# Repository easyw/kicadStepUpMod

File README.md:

kicadStepUp-WB
==============

KiCad **StepUp tools** are a FreeCAD Macro and a FreeCAD WorkBench to help in **Mechanical Collaboration** between **KiCad EDA** and **FreeCAD** or a **Mechanical CAD**.

**KiCad StepUp features:** 

- **load kicad board and parts in FreeCAD and export it to STEP** (or IGES) for a full ECAD MCAD collaboration
- **load kicad_mod footprint in FreeCAD to easy and precisely align the mechanical model to kicad footprint**
- **convert the STEP 3D model of parts, board, enclosure to VRML with Materials properties** for the best use in kicad
- **check interference and collisions** for enclosure and footprint design 
- **design a new pcb Edge with FreeCAD Sketcher and PUSH it to an existing kicad_pcb Board** 
- **PULL a pcb Edge from a kicad_pcb Board**, edit it in FC Sketcher and PUSH it back to kicad
- **design a new footprint in FreeCAD to get the power of Sketch in footprints**
- **generate Blender compatible VRML files**
- **translation infrastructure enabled**
- **auto-generate 3D FFC/FPC stiffener geometry from custom PCB user layers**

Please see [KiCad Info forum](https://forum.kicad.info/search?q=stepup) or [FreeCAD forum](https://forum.freecadweb.org/viewtopic.php?f=24&t=14276) to discuss or report issues regarding this Addon.

Installing
----------

Download and install your corresponding version of FreeCAD from [Download page](https://www.freecad.org/downloads) and either install

- automatically using the [FreeCAD Add-on Manager](https://github.com/FreeCAD/FreeCAD-addons) (bundled in to FreeCAD under Tools Menu)
  **(*) There is a known issue in FreeCAD Addons Manager on Linux**

- manually by copying the kicadStepUpMod folder to the Mod sub-directory of the FreeCAD application

- manually by following the standard installation [FreeCAD Installing more workbenches](https://wiki.freecad.org/Installing_more_workbenches)

StepUp Cheat sheet
------------------

[kicad StepUp Cheat sheet](https://github.com/easyw/kicadStepUpMod/raw/master/demo/kicadStepUp-cheat-sheet.pdf)

StepUp Videos
------------------

[ECAD-MCAD-collaboration: Complex Edge Sketch to PCB](https://youtu.be/eMdX3R9ni7g?t=1050)

[ECAD-MCAD-collaboration: Push&Pull Edge to PCB](https://youtu.be/n44iBpu_YjY)

[ECAD MCAD Synchronization: Push & Pull model placement in 3D environment](https://youtu.be/6R6UEUScjgA)

[ECAD-MCAD-collaboration: Footprint in FreeCAD](https://youtu.be/eMdX3R9ni7g?t=839)

[ECAD-MCAD-collaboration: FreeCAD + KiCAD complete walkthrough design](https://www.youtube.com/watch?v=ov3PpaP9uHI)

[ECAD-MCAD-collaboration: Designing a Complex PCB Edge from a 3D model Enclosure](https://www.youtube.com/watch?v=pJCeprBhWLs)

### Requirements

- **FreeCAD** **0.19, 0.20, 0.21, 0.22, 1.0**

- **KiCAD** **5.1**, **6.x**, **7.x**, **8.x**, **9.x**, **10.x**

- **KiCAD *10.99 nigthly* (partially supported)**

### Known issues

- on Linux *FreeCAD Snap and Flatpak* you may need to use 'mount bind' to have access to KiCad 3D models path

- on Linux *FreeCAD Addons* may fail to install (FC >= 1.0.1)

### License

[GNU AFFERO GENERAL PUBLIC LICENSE](https://www.gnu.org/licenses/agpl-3.0.en.html)

### Contributing to kicadStepUp

> :no_entry_sign: **AI-generated contributions are not accepted.** All Pull Requests and issues must be written genuinely by the contributor. :no_entry:We do not accept content (code, comments, commit messages, issue or PR descriptions, documentation, etc.) that is generated by :robot:AI tools. Such contributions will be rejected.

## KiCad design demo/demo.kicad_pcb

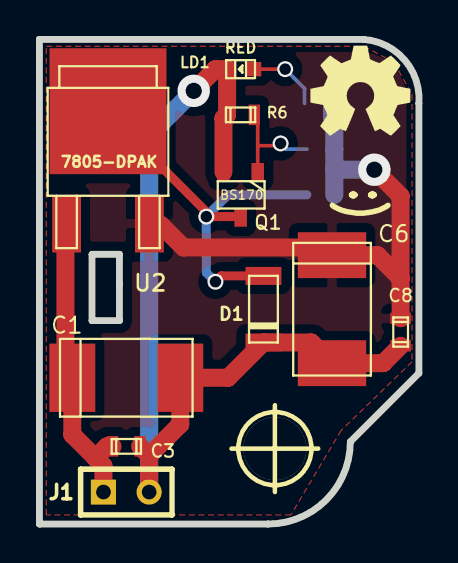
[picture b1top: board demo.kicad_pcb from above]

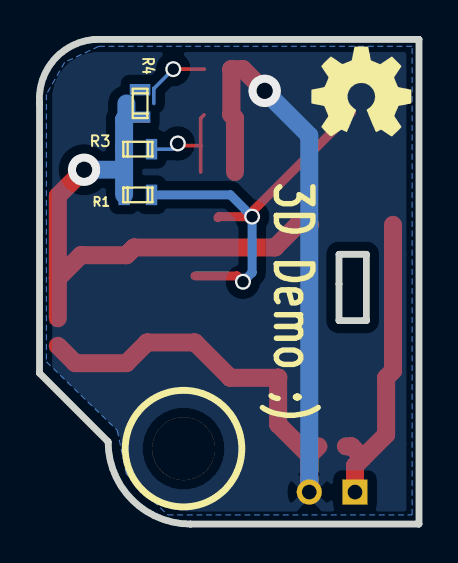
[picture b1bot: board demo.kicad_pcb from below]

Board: 2 copper layers, 21.1 x 26.9 mm, 14 parts (3 on the bottom side), 6 nets.

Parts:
C1, C6: 47u; c_tant_D
C3, C8: 100N; cap_0603
D1: 1N4148; sod80c
J1: Alim; SIL-2
LD1: RED; Led_0603
Q1: BS170; SOT23-GSD
R1, R4: 470; r_0603
R3: 12K; r_0603
R6: 1K; r_0603
U2: 7805-DPAK; d-pak
hole_3mm5: VAL**; hole_3mm5

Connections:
5V: C6.1, C8.1, R1.1, R3.1, R4.1, U2.3
+12V: C1.1, C3.1, J1.1, U2.1
ENP: Q1.1, R3.2, R6.1
GND: C1.2, C3.2, C6.2, C8.2, D1.2, J1.2, LD1.2, Q1.2, R6.2
unnamed: D1.1, Q1.3, R1.2, U2.2
unnamed: LD1.1, R4.2

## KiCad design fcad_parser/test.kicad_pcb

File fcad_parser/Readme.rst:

========================================
Python S-Expression Parser for KiCAD PCB
========================================

Intrudction
___________

The parser ``KicadPCB`` are written using a python S-Expression parser, the
sexp_parser_. To get this submodule, after checkout this repository, do ::

    git submodule init
    git submodule update

The ``KicadPCB`` parser shall be able to handle both ``kicad_pcb`` and
``kicad_mod`` file. The parser does not perform semantic check, though. For
that you'll need to write a large collection of sub-parsers that handle every
possible keyword. It'll be very tedious, but still easy with the help of
``SexpParser``. Check out the `sample code here`_.

.. _sexp_parser:  http://github.com/realthunder/sexp_parser
.. _sample code here: http://github.com/realthunder/sexp_parser/tree/master/test.py

Usage
_____

To get the python object model of a ``kicad_pcb`` or ``kicad_mod`` file ::
    
    from kicad_parser import KicadPCB
    pcb = KicadPCB.load(filename)

Check for error ::

    for e in pcb.getError():
        print('Error: {}'.format(e))

You can modify, add, or delete any expressions inside. You can use ``.`` to
access any non numerical keys such as ::

    pcb.general.zone

For numerical keys, and in fact, all type of keys, you can use ``[]`` ::

    pcb['layers']['0']

Or ::

    pcb.layers['0']

But not ::

    pcb.layers[0]

Because for ``(layers ( 0 F.cu single) ...)`` expression here, the ``0`` is
treated as a string key instead of an integer index. 

For multiple instances with the same key at the same level, you should access
the value by integer index, such as ::

    pcb.module[0]

For un-named values (i.e. any atom behind the key), use their appearance index
for accessing, skipping any named values. For example, to access an expression
like ``(drill oval 1.0 2.0)`` ::

    drill.oval
    drill[0] == 1.0
    drill[1] == 2.0

The 'oval' above would normally be treated as an un-named value, too. However,
``KicadPCB`` treats several special un-named values as named boolean type
value.  Their appearance in the S-Expression source means ``True``, otherwise
means ``False``. These expressions are always accessible through the object
model regardless of their appearance in the source. When doing ``export()``,
those ``False`` values will be ignored. These special values are ::

    gr_text.hide
    pad.drill.oval
    module.locked

This list is obviously not complete. But, it's easy to add your own mappings.
Check out the source code `here <kicad_pcb.py>`_

``KicadPCB`` also treats specal keyword as un-named boolean type, they are ::

    'yes', 'Yes', 'true', 'True', 'no', 'No', 'false', 'False'

To list the sub keys of a composite expression ::

    for subkey in pcb:
        print(subkey)

It will also list integer keys for un-named values if there is any.

To delete an expression ::

    del pcb.layers['0']

To create expressions, you'll need to import the general S-Expression Parser ::

    from kicad_parser import *

For multiple expressions with the same key, they will be stored into an object
of type ``sexp_parser.SexpList`` the parser will automatically create this list
object to hold the multiple instances. To check if it is a list ::

        isinstance(pcb.module,SexpList)

To add a simple expression ``(0 new.layer signal)``, ::

    pcb.layers['0'] = Sexp('0',[ 'new.layer', 'signal' ])

Note that if there is already an expression with the same key, ``=`` will not
overwrite the existing one. Instead, it will use ``SexpList`` to hold multiple
instances

To add a composite expression ::

    pcb.module[0].model = SexpParser(parseSexp(
        """(model new/model3 
            (at (xyz 1 2 3)) 
            (scale (xyz 3 5 6)) 
            (rotate (xyz 7.0 8.0 9.0)))
        """)

If you are not sure whether a key in the object model holds a single expression
or multiple instances, you can use ``SexpList`` to make sure it is a list ::

    if 'module' in pcb:
        for m in SexpList(pcb.module):
            print(m)

``KicadPCB`` will ensure several common keys to be presented even if there is
none, in which case an empty ``SexpList`` will be inserted. And if there is
only one instance, it will still be inside a ``SexpList``.  This is to spare
the pain of the boilerplate code above. The default keys are ::

    net
    net_class
        add_net
    dimension
    gr_text
    gr_line
    gr_circle
    gr_arc
    gr_curve
    segment
    via
    module
        fp_text
        fp_line
        fp_circle
        fp_arc
        pad
        model

To export the modified object model back to kicad_pcb file ::

    pcb.export(filename)

Or to output stream ::

    pcb.export(sys.stdout)

To export any ``Sexp`` ::

    exportSexp(pcb.general,sys.stdout)

See sample code `here <test.py>`_ for more details.

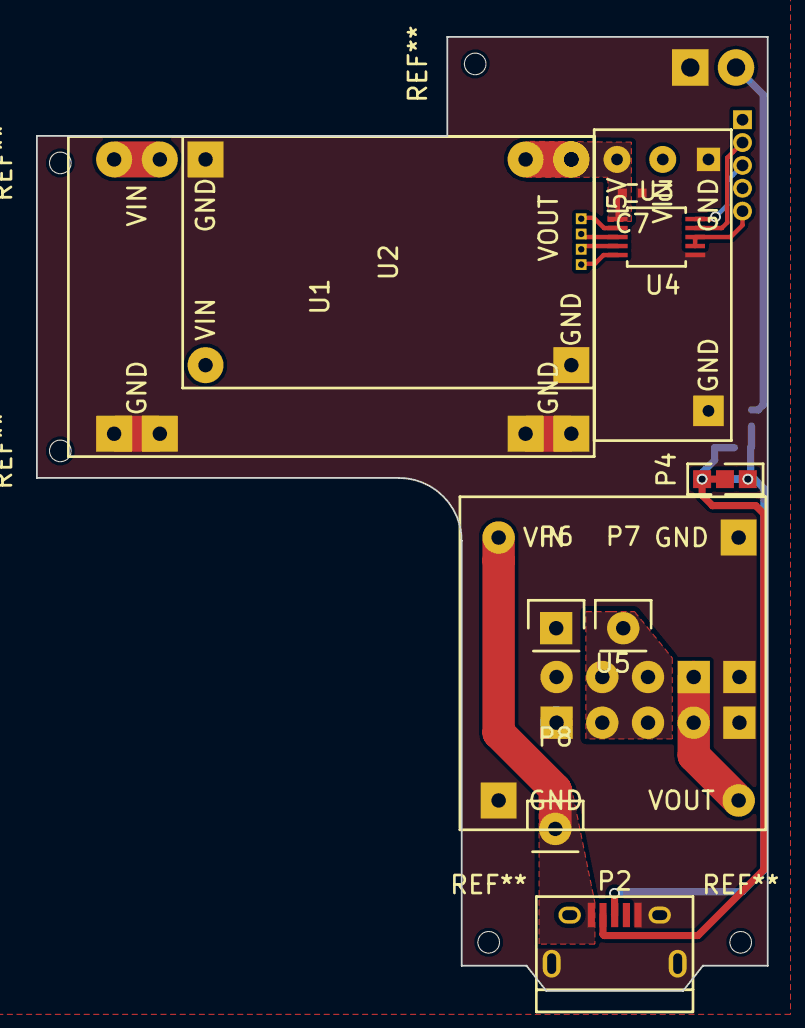
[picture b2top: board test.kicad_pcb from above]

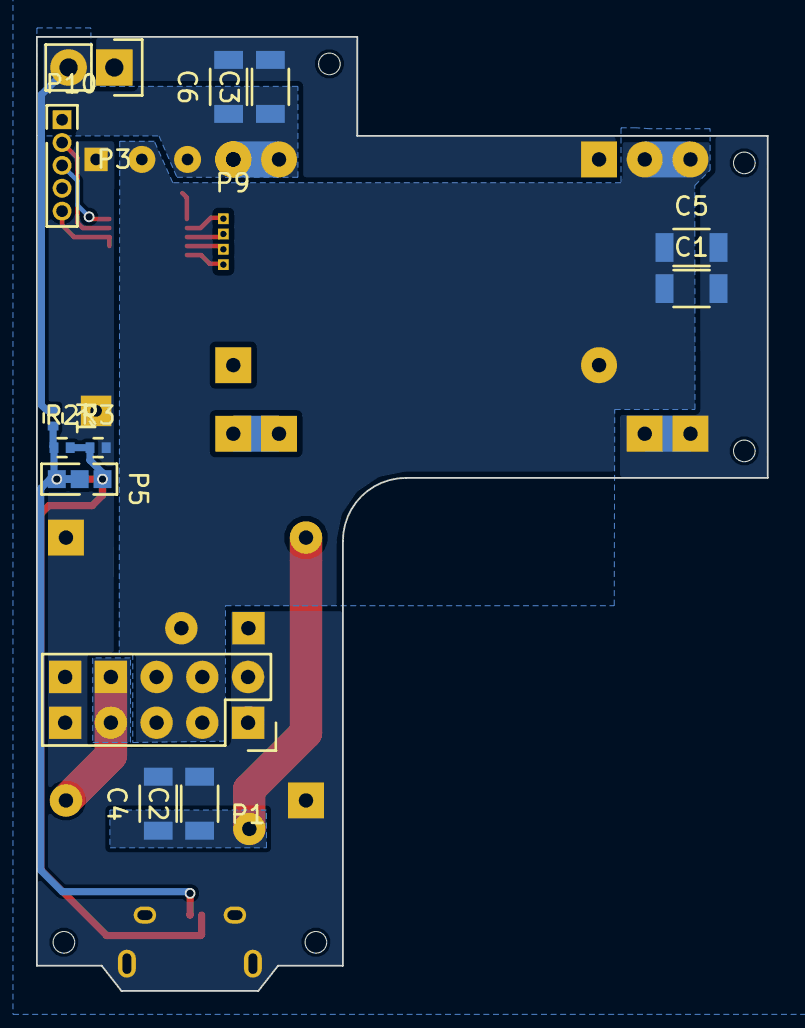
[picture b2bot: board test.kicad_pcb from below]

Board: 2 copper layers, 40.6 x 53.0 mm, 25 parts (14 on the bottom side), 14 nets.

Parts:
C1, C2, C3, C4, C5, C6: 47uF; C_1206
C7: 100nF; C_0402
P1: CONN5; Socket_Strip_Straight_2x05
P2: USB_Micro; USB_Micro-B
P3: CONN_VCC; Socket_Strip_Straight_1x02
P4, P5: CONN_01X03; Pin_Header_Straight_1x03_Pitch1.27mm
P6, P7, P8: CONN_01X01; Pin_Header_Straight_1x01
P9: CONN_01X02; Pin_Header_Straight_1x04_Pitch1.27mm
P10: CONN_01X05; Socket_Strip_Straight_1x05_Pitch1.27mm
R1: 2M; R_0402
R2: 1M; R_0402
R3: 400K; R_0402
U1: TPS61800 module; DCDC_Conv_TPS61088_Boost
U2: G5177 module; DCDC_Conv_G5177-Boost
U3: TMP432; TSSOP-10_3x3mm_Pitch0.5mm
U4: LDO_3V5; LDO_RT9018
U5: TP5000 Charger; DCDC_Charger-TP5000-Bucket

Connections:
/BAT: C1.1, C5.1, P1.3, P1.4, P1.5, P1.6, P7.1, U1.2, U2.2, U4.2
/CHARGE: P1.7, P1.8, U5.3
/CHG_IN: C2.1, C4.1, P2.1, P8.1, U5.2
/D1+: P9.1, U3.2
/D1-: P9.2, U3.3
/D2+: P9.3, U3.4
/D2-: P9.4, U3.5
/SCL1: P10.3, U3.10
/SDA1: P10.2, U3.9
/TMP_INT: P10.5, U3.7, U3.8
/V0.6: P2.2, P4.1, P4.2, P5.1, R2.2, R3.1
/V3.3: P2.3, P4.3, P5.2, P5.3, R1.2, R2.1
GND: C1.2, C2.2, C3.2, C4.2, C5.2, C6.2, C7.1, P1.1, P1.2, P1.9, P1.10, P2.5, P2.6, P3.1, P6.1, R3.2, U1.1, U2.1, U3.6, U4.1, U5.1
VCC: C3.1, C6.1, C7.2, P3.2, R1.1, U1.3, U2.3, U3.1, U4.3

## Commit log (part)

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2020-01-30 allowed import stpz on ksu button
2020-02-10 aligning commit nbr
2020-02-12 taper fp supported in load copper
2020-02-14 final fix for trapezoidal pads
    thx to realthunder
2020-03-13 Multiple 3D model paths
    Add ability to search multiple paths for 3D models.
    Multiple paths can be configured in 'main 3D folder location' and 'secondary 3D folder loc' fields.
    These 2 fields can be comma or carriage return separated lists of paths.
    Currently multiple paths in these fields must be manually entered and not by using the '...' button.
2020-03-14 Import KiCAD prefs environment paths
    New kicadStepUpGui pref 'KiCAD prefs folder' to allow users to select the folder containing file 'kicad_common'.
    File 'kicad_common' is parsed for environment variables with absolute paths.
    The paths are then used to perform substitutions in the 3D model path.
    This modification could make 'main 3D folder location' obsolete since KISYS3DMOD is an entry in the kicad_common file.
    Also since the ALT3DMOD pref now accepts a list of paths (comma or CR separated) then that field can be used to search other external paths for 3D models.
    Note: The preferences panel layout could use some adjustment since they are now a bit compressed together (I don't fully under
2020-04-07 shifting the check for new STEP importer to the end of June
2020-04-12 Allowing simple copy of Body
2020-05-06 improved extra sketches importing
2020-05-07 aligning commit numbers for checking updates
2020-06-25 fixing new github page format
2020-06-30 improved BlackList interface
    allowing height, volume and list parameters in logical 'and'
2020-07-08 implemented fp_rect for fp loading
2020-11-29 Changed regular expression to allow both keywords (footprint and module)
    Fixes #66
2020-11-30 updating kicad parser for 'footprint' and 'module' support (k 5.1 & 5.99)
2020-12-20 fixing fp exporter for 3d path including spaces
2020-12-22 Fix source typos
2020-12-25 minor typo fix
2021-01-29 fixing fill zone area
2021-02-20 updating push&pull 3d models to be compatible with k v5.99
2021-03-05 aligning release nbr
2021-04-08 new RF PolyLined sketcher generator for EM RF sw
2021-04-08 increasing discretization quality for RF conversion
2021-04-21 undo also on reset placement for a shape
2021-08-29 adding NetTie Poly, improved Pads Poly algo, added PTH & NPTH Drills tools for arc in drills, B_Cu layer option for Poly, shape(s) Contour command
2021-08-29 removing extra printing info
2021-08-29 added sample files to Demo Menu folder
2021-08-30 aligning commits
2021-08-31 improving loading fp drills
2021-08-31 cutting tracks outside pcb (castellated holes)
2021-09-03 support for: arc tracks, improved pad resolution and custom pads
2021-09-05 fix Connect Sketch issue
2021-09-06 Internal layers allowed for fp generation (not loading) padNbr for NetTie and Pads_Poly
2021-09-08 adding 3 points center and arc to circle sketch tools
2021-09-09 fixing colors for 2d objects
2021-09-13 second try for fixing Darftmakesketch FC issue
2021-09-15 minor fix in assigning padNbr
2021-09-16 allowing padNum and padNbr tag
2021-09-24 minor fix for pushing keepout zone sketch
2021-09-29 fully integration of fcad_pcb tools from @realthunder
2021-09-29 fix for top tracks and zones z-placement
2021-10-03 Holes for vias are created when importing PCB.
2021-10-19 enabling Transparency in STP color models
2021-10-21 slightly align some color and transparency on materials
2021-10-25 reverting transparency on step export, adding undo on export 3d model
2021-10-27 export 3D STEP models w transparency + minor fix for importing keepout zones
2021-10-28 rem,oving old kicad site references on docs
2021-10-28 aligning version
2021-10-28 keeping transparency for single shape object in 3d exporting materials
2021-10-28 kv6 new arc.mid format compat
2021-10-29 arc rework for pcbnew version >= 20211014
2021-10-30 fixing drill parsing when drill is missing
2021-11-04 fixing offset and oval drills for bottom pads
2021-11-11 adding the solid check in step exporting of a step model
2021-11-15 giving stpz priority to stp in load models
2021-11-17 fixing timestamp push pull
2021-11-22 improving 3d model searching up to 4 paths
2021-11-25 fixinf fp_arc for kv6 format
2021-12-01 minor fix in fp loading for bottom tech layers
2021-12-02 reverting last commit (issues in p.drill parsing)
2021-12-15 utf-8 compat
2021-12-16 fixing utf-8 issue on loading board
2021-12-23 minor fix for turntable and adding xml metafile
2022-01-10 adding Undo on loading pcb/tracks to avoid issues on deleting objects
2022-01-10 Ignore errors when loading primitives
    Loading tracks for my PCB design leads to:
    17:23:32 Running the Python command 'ksuToolsAddTracks' failed:
    Traceback (most recent call last):
    File "/home/user/.FreeCAD/Mod/kicadStepUpMod/kicadStepUpCMD.py", line 3415, in Activated
    tracks.addtracks()
    File "/home/user/.FreeCAD/Mod/kicadStepUpMod/tracks.py", line 346, in addtracks
2022-01-15 fixing zoom fit for tracks
2022-02-19 minor fix on tracks loading (linux)
2022-03-14 fixing pcb thickness = 0 due to new stack feature fixing regression in replacing sketch in board loading
2022-03-17 fixing some push-pull kv6-kv7 format changes
2022-03-19 fixing tracks cutting
2022-03-23 fixing complex sketch pushing
2022-03-23 fixing push complex sketches
2022-04-04 forcing {:.6f}".format for pushing pcb to avoid DRC errors on edge
2022-04-30 fixing parsing pad without drill but with drill offset
2022-05-11 create colored Binder object
2022-05-16 minor improvement in pushing pcb edge
2022-05-31 subshapebinder relinker tool
2022-05-31 updating version
2022-06-13 not showing fp models when 3D model is set to hide
2022-06-27 fixing loading virtual modules for kv >= 6
2022-07-13 improving suggestion for FC import settings (FC0.20+)
2022-07-19 fixing a typo in condition (kSU)
2022-07-22 improving warning for STEP import settings
2022-07-23 Initial commit for translate WB
2022-07-28 fixing add tracks in case of no holes
2022-07-30 avoid error in case of 0-lenght tracks
2022-08-29 fixing Assembly3 Link import option adding Snap Flatpack compatibility hint
2022-08-30 moving LCS to main Board container for a better compatibility with Assembly 4 WB
2022-08-30 fixing report and compare of sketches
2022-09-30 fixing reset placement and virtual objs in kv6
2022-10-03 adding Faces to shape info command
2022-10-10 fixing tracks placement if not zero
2022-10-13 command to create a BoundBox shape
2022-10-14 improving boundbox command
2022-10-20 minor fix on pushing pdb edge
2022-10-24 improving moving sketch w/ resetting placement
2022-12-27 adding whitelist in preferences and loading 3d models
2022-12-28 adding whitelist to cheat sheet
2023-01-16 fixing resetting placement for STEP merge importing on FC0.20, adding undo feature
2023-02-09 fixing help on dark themes, zero length arcs
2023-02-09 minor fix dark theme
2023-03-24 new fpimporter based on fcad_pcb
2023-03-29 adding NetTie in fp loader
2023-03-30 adding hollow-pad mod sample file
2023-03-31 improving pads for net ties fp_poly shapes
2023-04-03 improving reset Placement for Part kSU models
2023-04-04 minor improvement of kSU tools menu
2023-04-19 improving tracks loading an some more
2023-05-17 fixing reset Part placement for ot kSU objects
2023-05-18 adding Snap FlatPack dialogs option
2023-05-20 fix in load fp line color
2023-07-31 skip adding hidden 3d models of component
2023-08-02 no popups
2023-08-31 changed the name of pref text edit
2023-09-22 fixing rotation for fp loader, colors for transforming plc, pushing 3d models
2023-10-10 fixing some pcb drill issue, adding internal legacy dxf lib
2023-10-14 makefacedxf returning to Part::FaceMakerBullseye (fixing memory leak?)
2023-10-16 force re-meshing for vrml exporting
2023-10-17 fixing new var declaration
2023-10-28 cheat-sheet: regenerate pdf
    Regenerate the PDF file using the most recent version of the ODF file.
2023-11-02 reverting tracks to be compatible w/ previous FC versions
2023-11-08 allowing gr_poly for arcs (push&pull)
2023-11-13 minor fix for loading tracks
2023-11-19 opt out option for tracks and vias
2023-11-24 improved page tooltips for blacklist 3D models
2023-12-04 better implementation of push function (avoiding re) for kv8 compat
2023-12-16 improved method to get commits number
2023-12-25 FC0.18 compatibility fix
2023-12-28 adding a msg to use of urllib cmtnum=635
2024-01-19 fixing pushing fp for kv7 cmtnum=637
2024-01-29 fixed skipping of virtual 3d models cmtnum=638
2024-02-13 fixing utf-8 coding in kicad parser for fp cmtnum=639
2024-02-27 zones named after sketch name
2024-03-11 Add Spanish translation
    Added es-ES translations
2024-03-12 Add Spanish Translation
2024-03-28 Directly open KiCadStepUp preferences page when running `ksuToolsEditPrefs`
    Is possible to open the preference page that was added using
    `addPreferencePage()` command
2024-04-13 Don't change foreground color of help text
    - Previously it got black text on dark theme.
    - Seems to work in both light and dark themes.
2024-04-21 aligning commit num cmtnum=653
2024-05-02 removing all PySide2 calls cmtnum=655
2024-05-23 Search for Combo View in a loop
2024-06-03 aligning cmt num cmtnum=661
2024-06-17 better kv5-8 compat push pcb cmtnum=663
2024-06-18 improved kv8 speed & compat push pcb cmtnum=665
2024-07-16 improved kv8 compat push fp uuid cmtnum=667
2024-08-26 improved kv8 compat import fp uuid cmtnum=669
2024-09-13 speeding up 3D model pushing cmtnum=671
2024-09-20 adding helping video liks to help and readme cmtnum=673
2024-09-23 adding helping video links to readme cmtnum=676
2024-09-23 adding helping video links to readme cmtnum=678
2024-11-03 FreeCAD 1.0 RC2 fix: use CAM module instead of Path
2024-11-04 improving Sketch conversion cmtnum=683
2024-11-25 Update translations from CrowdIn
2024-11-30 fixup! Update translation script
2024-12-04 adding gif for tutorial cmtnum=692
2025-01-16 improving kv8 3D model pushing position cmtnum=694
2025-03-03 adding some 3d tools, fixing CAM
2025-03-20 mending stp files for FC1.0 num cmtnum=699
2025-04-03 emulating CAM.Area for FC1.0 num cmtnum=701
2025-04-03 aligning commit num cmtnum=703
2025-04-07 Show/Hide hidden models num cmtnum=705
2025-04-14 amending STEP/stpZ transparency exporter for FC1.0 only num cmtnum=707
2025-04-15 improved sex_parser for kv9 lock fp num cmtnum=709
2025-04-22 fixing widget for FC new themes num cmtnum=711
2025-07-06 allowing relative paths to configured folder cmtnum=713
2025-08-27 commit_num.py: fix Python SyntaxWarning
    Python (3.13) logs the following warning:
    ./commits_num.py:13: SyntaxWarning: invalid escape sequence '\d'
    return re.search('\d+$', res.links['last']['url']).group()
    ./commits_num.py:52: SyntaxWarning: invalid escape sequence '\d'
    commit = response.json()[0]; commit['number'] = re.search('\d+$', response.links['last']['url']).group()
2025-09-07 fixing reset position Qt6 cmtnum=715
2025-09-29 aligning commit num cmtnum=720
2025-11-20 fixing backslash for some 3D path commit num cmtnum=722
2025-11-30 aligning version num commit num cmtnum=726
2025-12-14 FC1.2 com pat pushing 3D models num commit num cmtnum=729
2025-12-29 Add utils with mk_str / mk_uni functions
2025-12-29 Replace make_unicode_t with common mk_str
2025-12-29 Rename to mk_str/mk_uni to more common make_string/make_unicode
2026-01-27 cheat sheet: Fix some broken links in cheat sheet
2026-04-30 config: add pyproject.toml (ruff, ty, uv), pre-commit, CI, dependabot, editorconfig
    - pyproject.toml: ruff lint + format (py311, 120 cols, 20 rule sets),
    ty type checker, uv config
    - .pre-commit-config.yaml: ruff lint/fix + ruff-format + ty + standard hooks
    - .github/workflows/ci.yml: 3 jobs (ruff lint+format, pre-commit, ty)
    - .github/dependabot.yml: weekly updates for actions and pip
    - .editorconfig: 4-space indent, LF, UTF-8
2026-04-30 fix: manual semantic fixes (SIM103, SIM115, PERF402, Copilot comments, etc.)
    Manual fixes across 19 files:
    - SIM103: inline boolean returns (kicadStepUpCMD, kicadStepUptools)
    - SIM115: with statements for file handles (exchangePositions, fps,
    kicadStepUptools, kicad_parser)
    - SIM113: enumerate() replaces manual counters (kicadStepUptools, tracks)
    - PERF402: .extend() replaces manual list copy loops (constrainator,
